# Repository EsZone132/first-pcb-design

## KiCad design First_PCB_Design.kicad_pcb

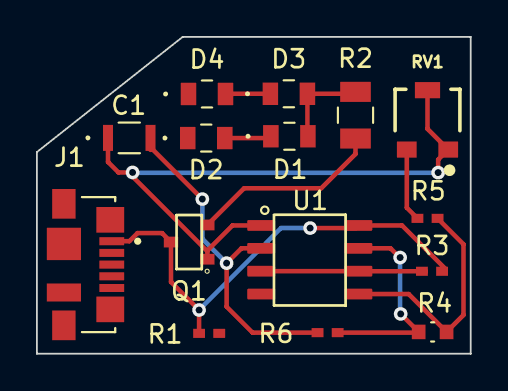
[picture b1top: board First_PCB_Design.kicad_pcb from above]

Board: 2 copper layers, 24.1 x 17.6 mm, 15 parts (0 on the bottom side), 12 nets.

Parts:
C1: 22uF; C2012JB1A226M125AB
D1, D2, D3, D4: BLUE; VAOL-S8SB4
J1: USB_B_Micro; MOLEX_47346-0001
Q1: SS8050-G
R1, R3, R6: 27k; RC0402JR-0727KL
R2: 100; RNCP1206FTD100R
R4: 100k; RC0603FR-07100KL
R5: 30k; RC0402JR-0730KL
RV1: 20k; TRIM_PVG3A200C01R00
U1: LM358BAIDR; LM358BAIDR-SOIC

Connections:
-INA: C1.2, R6.2, U1.2 (-In_A)
GND: D2.1 (K), D4.1 (K), J1.5 (GND), R1.2, U1.4 (GND)
unnamed: D1.1 (K), D2.2 (A)
unnamed: D1.2 (A), D3.2 (A), R2.2
unnamed: D3.1 (K), D4.2 (A)
unnamed: Q1.2, R2.1
unnamed: R3.2, U1.3 (+In_A), U1.6 (-In_B)
unnamed: R4.1, R6.1, U1.7 (Out_B)
unnamed: R4.2, R5.1, U1.5 (+In_B)
unnamed: R5.2, RV1.3
OutA: C1.1, Q1.1, RV1.1, RV1.2, U1.1 (Out_A)
VCC: J1.1 (VBUS), Q1.3, R1.1, R3.1, U1.8 (V+)

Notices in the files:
parts and their libraries:
Copyright 2021 Accelerated Designs. All rights reserved.
